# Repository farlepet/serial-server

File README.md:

Network-Connected Serial Server
===============================
This project intends to develop a simple and (relatively) low-cost Linux-based
network-connected (Ethernet or WiFi) serial (RS-232) device, that can act as
either a console server, or emulate a serial device such as a modem.

Intended hardware features
* Multiple power sources
  * PoE
  * USB (also doubles as serial debug port)
  * External power
* WiFi connection
  * Planning on ESP32-C3 via SPI (and maybe UART as fallback)
  * Use [esp-hosted](https://github.com/espressif/esp-hosted) to interface with Linux
  * Likely won't need any external flash, may design in the option just in case
* Ethernet connection
  * At least 10/100, undecided on specifics, SG2002 should already have a PHY,
    so should just need the port and magnetics (if not integrated, needs to
    support PoE).
* Linux-capable CPU
  * Planning on using SG2002 RISC-V SOC
  * Running Linux off of micro-SD card
    * Possible option for SPI flash?
* RS-232 via DE-9
  * Port pinout is as a DCE, as this is the most likely scenario in which the
    ring indicator would be useful. NULL-modem cable/adapter can be used to switch
    to DTE pinout.
  * Using MAX3237 transceiver to allow full functionality while in DCE mode
  * Headers availble to allow for custom daughter boards for different protocols
* Status LEDs
  * Separate serlal RX and TX LEDs
  * Possible ring-indicator LED
  * Possible "remote access active" LED
* Possibly integrating a security chip like the ATECC
* Possibly hardware watchdog

Use of third-party symbols/footprints
-------------------------------------

The following footprints were obtained from Digi-Key:
 * Amphenol 10067099-400LF: https://www.digikey.com/en/models/4238740

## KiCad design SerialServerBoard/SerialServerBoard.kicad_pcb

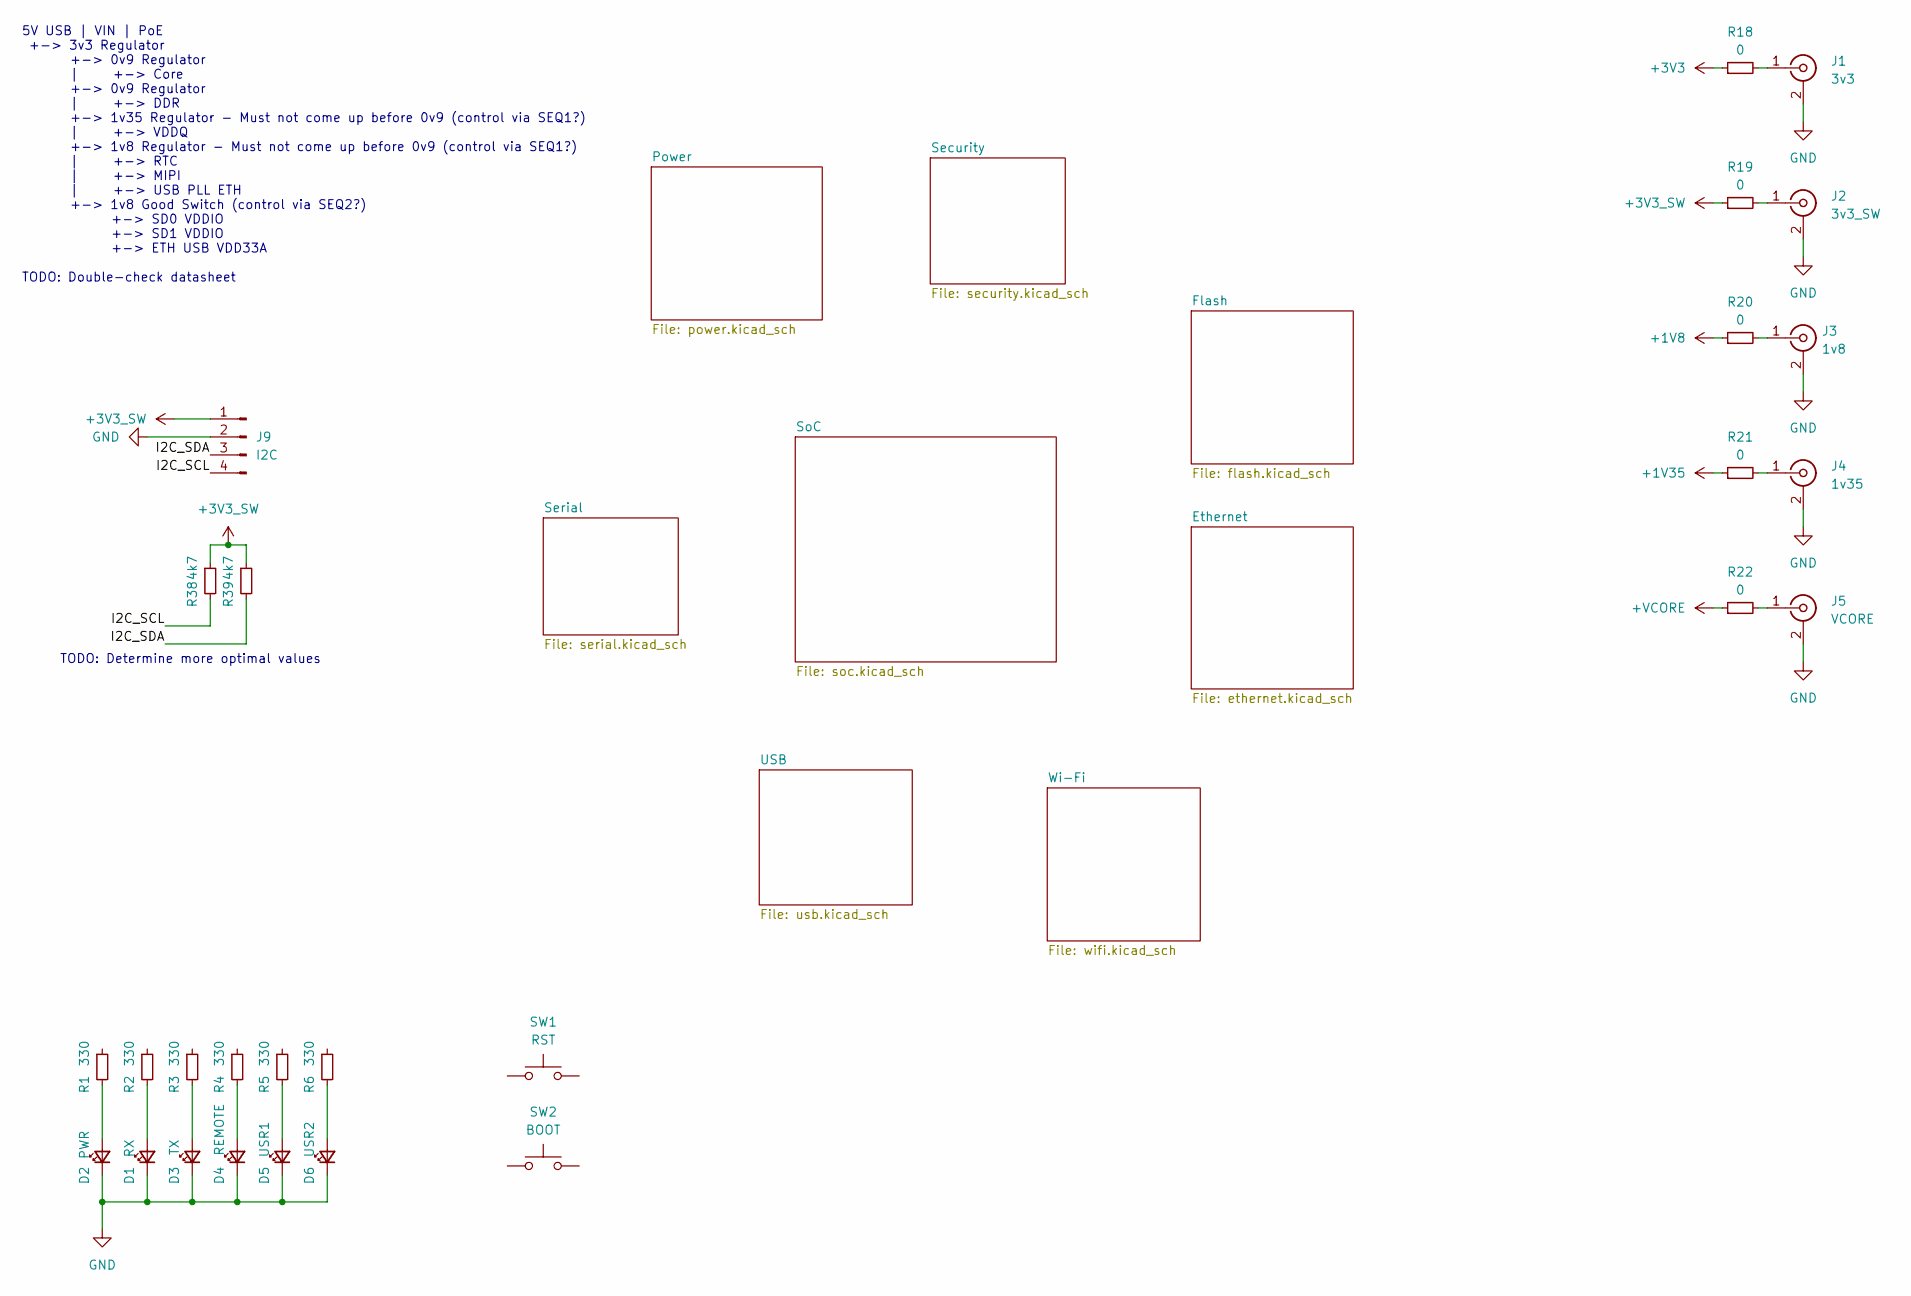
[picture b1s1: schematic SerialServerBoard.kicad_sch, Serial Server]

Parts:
D1: RX; LED_0603_1608Metric
D2: PWR; LED_0603_1608Metric
D3: TX; LED_0603_1608Metric
D4: REMOTE; LED_0603_1608Metric
D5: USR1; LED_0603_1608Metric
D6: USR2; LED_0603_1608Metric
J1: 3v3; TE_CONN_2337019-1
J2: 3v3_SW; TE_CONN_2337019-1
J3: 1v8; TE_CONN_2337019-1
J4: 1v35; TE_CONN_2337019-1
J5: VCORE; TE_CONN_2337019-1
J9: I2C; PinHeader_1x04_P1.27mm_Vertical
R1, R2, R3, R4, R5, R6: 330; R_0603_1608Metric
R18, R19, R20, R21, R22: 0; R_0402_1005Metric
R38, R39: 4k7; R_0603_1608Metric
SW1: RST
SW2: BOOT

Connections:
+1V8: R20.1; also elsewhere on the board
+1V35: R21.1; also elsewhere on the board
+3V3: R18.1
+3V3_SW: J9.1, R19.1, R38.1, R39.1; also elsewhere on the board
+VCORE: R22.1; also elsewhere on the board
/I2C_SCL: J9.4, R38.2
/I2C_SDA: J9.3, R39.2
GND: D1.1 (K), D2.1 (K), D3.1 (K), D4.1 (K), D5.1 (K), D6.1 (K), J1.2 (Ext), J2.2 (Ext), J3.2 (Ext), J4.2 (Ext), J5.2 (Ext), J9.2; also elsewhere on the board
unnamed: D1.2 (A), R2.2
unnamed: D2.2 (A), R1.2
unnamed: D3.2 (A), R3.2
unnamed: D4.2 (A), R4.2
unnamed: D5.2 (A), R5.2
unnamed: D6.2 (A), R6.2
unnamed: J1.1 (In), R18.2
unnamed: J2.1 (In), R19.2
unnamed: J3.1 (In), R20.2
unnamed: J4.1 (In), R21.2
unnamed: J5.1 (In), R22.2

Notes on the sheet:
TODO: Determine more optimal values
5V USB | VIN | PoE +-> 3v3 Regulator +-> 0v9 Regulator | +-> Core +-> 0v9 Regulator | +-> DDR +-> 1v35 Regulator - Must not come up before 0v9 (control via SEQ1?) | +-> VDDQ +-> 1v8 Regulator - Must not come up before 0v9 (control via SEQ1?) | +-> RTC | +-> MIPI | +-> USB PLL ETH +-> 1v8 Good Switc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

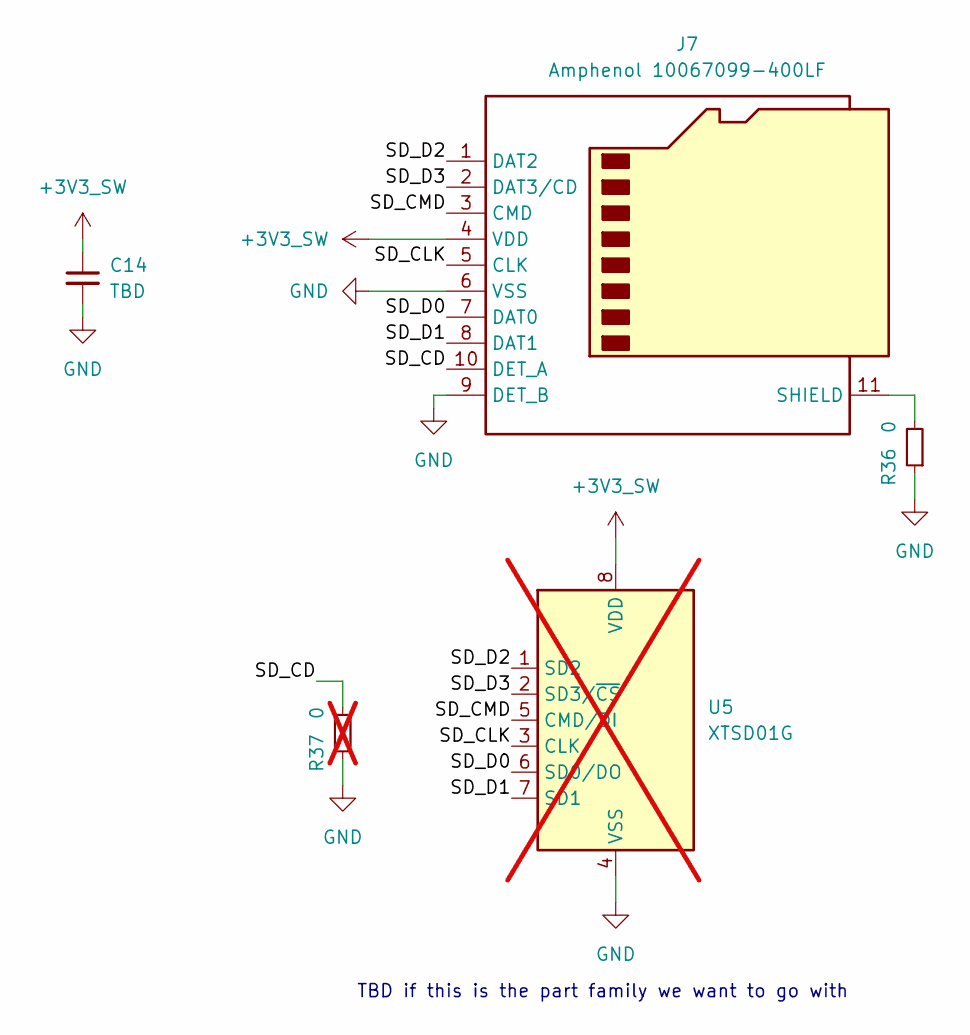
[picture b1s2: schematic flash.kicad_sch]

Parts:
C14: TBD; C_0603_1608Metric
J7: Amphenol 10067099-400LF; CONN8_10067099-400LF_FCI
R36: 0; R_0402_1005Metric
R37: 0; R_0402_1005Metric; not fitted
U5: XTSD01G; LGA-8_8x6mm_P1.27mm; not fitted

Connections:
+3V3_SW: C14.1, J7.4 (VDD), U5.8 (VDD); also elsewhere on the board
/Flash/SD_CD: J7.10 (DET_A), R37.2
/Flash/SD_CLK: J7.5 (CLK), U5.3 (CLK)
/Flash/SD_CMD: J7.3 (CMD), U5.5 (CMD/DI)
/Flash/SD_D0: J7.7 (DAT0), U5.6 (SD0/DO)
/Flash/SD_D1: J7.8 (DAT1), U5.7 (SD1)
/Flash/SD_D2: J7.1 (DAT2), U5.1 (SD2)
/Flash/SD_D3: J7.2 (DAT3/CD), U5.2 (SD3/~CS)
GND: C14.2, J7.6 (VSS), J7.9 (DET_B), R36.1, R37.1, U5.4 (VSS); also elsewhere on the board
unnamed: J7.11 (SHIELD), R36.2

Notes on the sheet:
TBD if this is the part family we want to go with

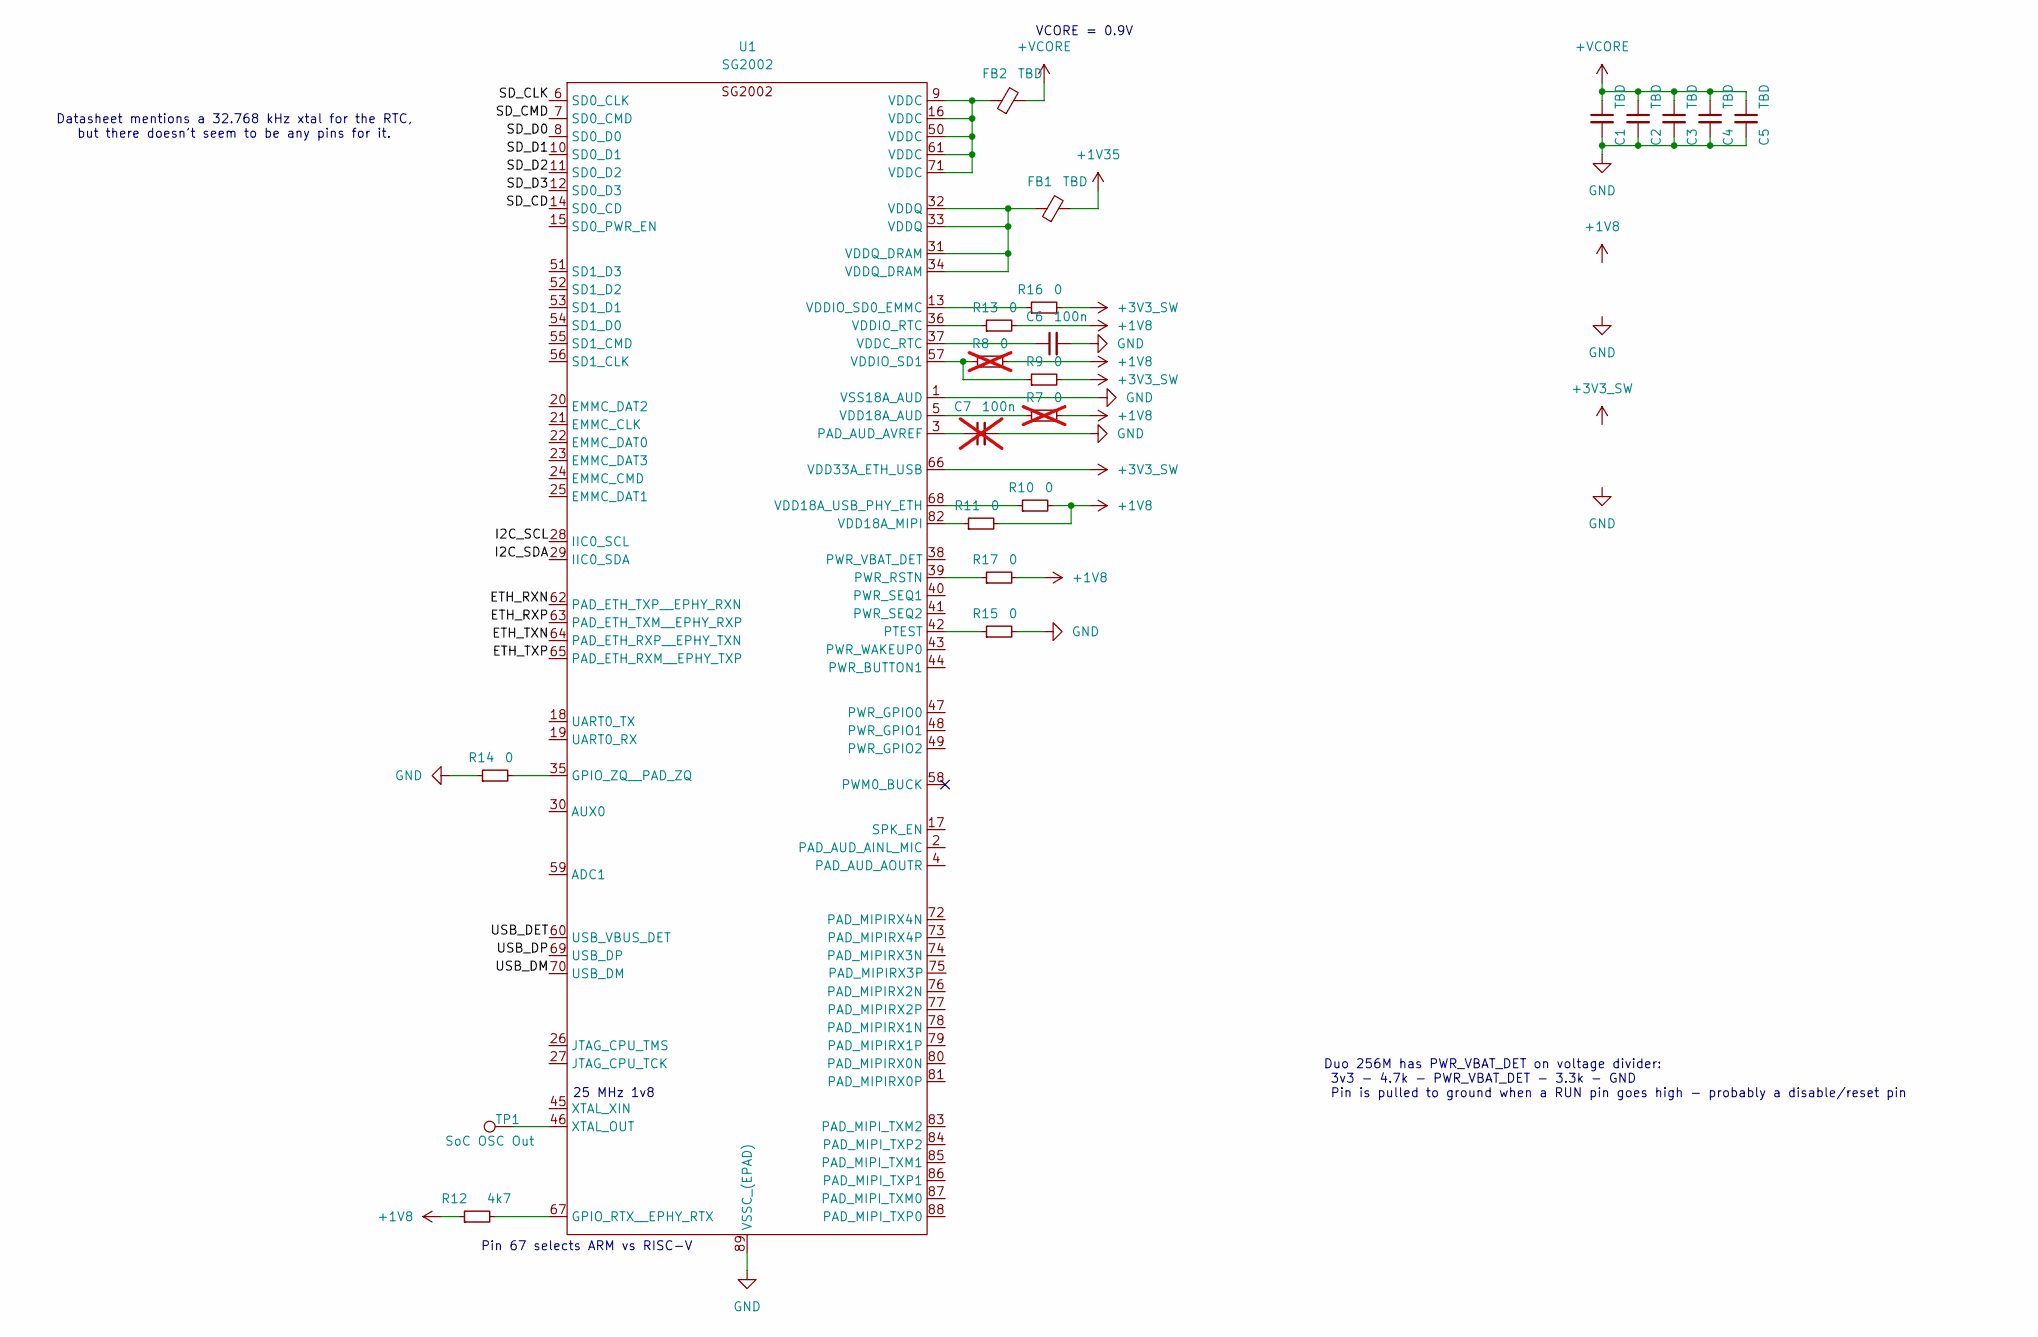
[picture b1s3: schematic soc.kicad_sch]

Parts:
C1, C2, C3, C4, C5: TBD; C_0603_1608Metric
C6: 100n
C7: 100n; not fitted
FB1, FB2: TBD; L_0603_1608Metric
R7, R8: 0; R_0402_1005Metric; not fitted
R9, R10, R11, R13, R14, R15, R16, R17: 0; R_0402_1005Metric
R12: 4k7; R_0603_1608Metric
TP1: SoC OSC Out
U1: SG2002; SG2002_QFN-88

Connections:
+1V8: R7.2, R8.2, R10.2, R11.2, R12.1, R13.2, R17.2; also elsewhere on the board
+1V35: FB1.2; also elsewhere on the board
+3V3_SW: R9.2, R16.2, U1.66 (VDD33A_ETH_USB); also elsewhere on the board
+VCORE: C1.1, C2.1, C3.1, C4.1, C5.1, FB2.2; also elsewhere on the board
/SoC/ETH_RXN: U1.62 (PAD_ETH_TXP__EPHY_RXN)
/SoC/ETH_RXP: U1.63 (PAD_ETH_TXM__EPHY_RXP)
/SoC/ETH_TXN: U1.64 (PAD_ETH_RXP__EPHY_TXN)
/SoC/ETH_TXP: U1.65 (PAD_ETH_RXM__EPHY_TXP)
/SoC/I2C_SCL: U1.28 (IIC0_SCL)
/SoC/I2C_SDA: U1.29 (IIC0_SDA)
/SoC/SD_CD: U1.14 (SD0_CD)
/SoC/SD_CLK: U1.6 (SD0_CLK)
/SoC/SD_CMD: U1.7 (SD0_CMD)
/SoC/SD_D0: U1.8 (SD0_D0)
/SoC/SD_D1: U1.10 (SD0_D1)
/SoC/SD_D2: U1.11 (SD0_D2)
/SoC/SD_D3: U1.12 (SD0_D3)
/SoC/USB_DET: U1.60 (USB_VBUS_DET)
/SoC/USB_DM: U1.70 (USB_DM)
/SoC/USB_DP: U1.69 (USB_DP)
GND: C1.2, C2.2, C3.2, C4.2, C5.2, C6.2, C7.2, R14.1, R15.2, U1.1 (VSS18A_AUD), U1.89 (VSSC_(EPAD)); also elsewhere on the board
unnamed: FB1.1, U1.31 (VDDQ_DRAM), U1.32 (VDDQ), U1.33 (VDDQ), U1.34 (VDDQ_DRAM)
unnamed: FB2.1, U1.9 (VDDC), U1.16 (VDDC), U1.50 (VDDC), U1.61 (VDDC), U1.71 (VDDC)
unnamed: R12.2, U1.67 (GPIO_RTX__EPHY_RTX)
unnamed: R14.2, U1.35 (GPIO_ZQ__PAD_ZQ)
unnamed: C7.1, U1.3 (PAD_AUD_AVREF)
unnamed: R15.1, U1.42 (PTEST)
unnamed: R17.1, U1.39 (PWR_RSTN)
unnamed: R7.1, U1.5 (VDD18A_AUD)
unnamed: R11.1, U1.82 (VDD18A_MIPI)
unnamed: R10.1, U1.68 (VDD18A_USB_PHY_ETH)
unnamed: C6.1, U1.37 (VDDC_RTC)
unnamed: R13.1, U1.36 (VDDIO_RTC)
unnamed: R16.1, U1.13 (VDDIO_SD0_EMMC)
unnamed: R8.1, R9.1, U1.57 (VDDIO_SD1)
unnamed: TP1.1, U1.46 (XTAL_OUT)

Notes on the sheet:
Pin 67 selects ARM vs RISC-V
Datasheet mentions a 32.768 kHz xtal for the RTC, but there doesn't seem to be any pins for it.
Duo 256M has PWR_VBAT_DET on voltage divider: 3v3 - 4.7k - PWR_VBAT_DET - 3.3k - GND Pin is pulled to ground when a RUN pin goes high - probably a disable/reset pin
25 MHz 1v8
VCORE = 0.9V

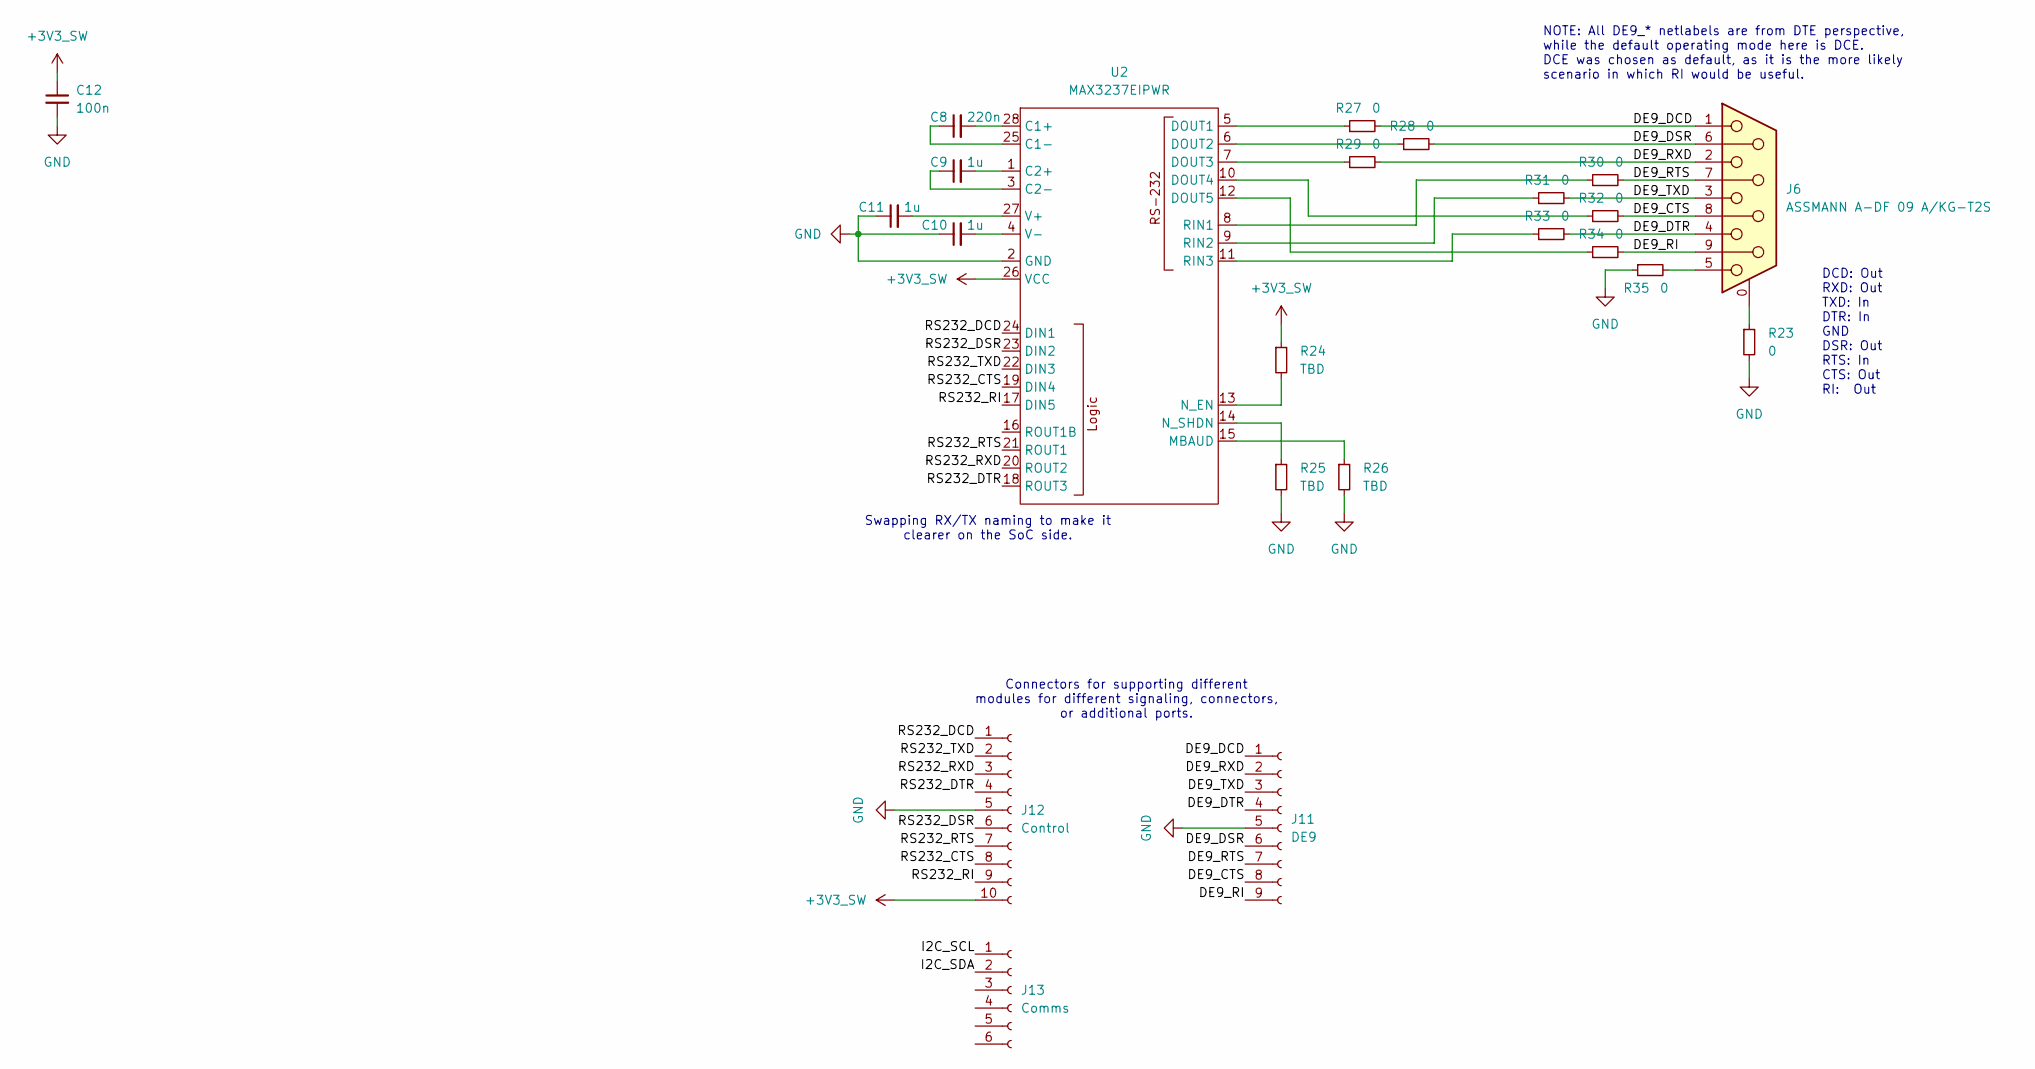
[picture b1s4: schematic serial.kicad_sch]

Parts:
C8: 220n; C_0603_1608Metric
C9, C10, C11: 1u; C_0603_1608Metric
C12: 100n; C_0603_1608Metric
J6: ASSMANN A-DF 09 A/KG-T2S; ASSMANN_A-DF_09_A_KG-T2S
J11: DE9; PinHeader_1x09_P1.27mm_Vertical
J12: Control; PinHeader_1x10_P1.27mm_Vertical
J13: Comms; PinHeader_1x06_P1.27mm_Vertical
R23, R27, R28, R29, R30, R31, R32, R33, R34, R35: 0; R_0402_1005Metric
R24, R25, R26: TBD; R_0402_1005Metric
U2: MAX3237EIPWR; TSSOP-28_4.4x9.7mm_P0.65mm

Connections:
+3V3_SW: C12.1, J12.10, R24.1, U2.26 (VCC); also elsewhere on the board
/Serial/DE9_CTS: J6.8, J11.8, R32.2
/Serial/DE9_DCD: J6.1, J11.1, R27.2
/Serial/DE9_DSR: J6.6, J11.6, R28.2
/Serial/DE9_DTR: J6.4, J11.4, R33.2
/Serial/DE9_RI: J6.9, J11.9, R34.2
/Serial/DE9_RTS: J6.7, J11.7, R30.2
/Serial/DE9_RXD: J6.2, J11.2, R29.2
/Serial/DE9_TXD: J6.3, J11.3, R31.2
/Serial/I2C_SCL: J13.1
/Serial/I2C_SDA: J13.2
/Serial/RS232_CTS: J12.8, U2.19 (DIN4)
/Serial/RS232_DCD: J12.1, U2.24 (DIN1)
/Serial/RS232_DSR: J12.6, U2.23 (DIN2)
/Serial/RS232_DTR: J12.4, U2.18 (ROUT3)
/Serial/RS232_RI: J12.9, U2.17 (DIN5)
/Serial/RS232_RTS: J12.7, U2.21 (ROUT1)
/Serial/RS232_RXD: J12.3, U2.20 (ROUT2)
/Serial/RS232_TXD: J12.2, U2.22 (DIN3)
GND: C10.1, C11.1, C12.2, J11.5, J12.5, R23.2, R25.2, R26.2, R35.1, U2.2 (GND); also elsewhere on the board
unnamed: J6.0 (PAD), R23.1
unnamed: J6.5, R35.2
unnamed: C8.2, U2.28 (C1+)
unnamed: C8.1, U2.25 (C1-)
unnamed: C9.2, U2.1 (C2+)
unnamed: C9.1, U2.3 (C2-)
unnamed: R27.1, U2.5 (DOUT1)
unnamed: R28.1, U2.6 (DOUT2)
unnamed: R29.1, U2.7 (DOUT3)
unnamed: R32.1, U2.10 (DOUT4)
unnamed: R34.1, U2.12 (DOUT5)
unnamed: R26.1, U2.15 (MBAUD)
unnamed: R24.2, U2.13 (N_EN)
unnamed: R25.1, U2.14 (N_SHDN)
unnamed: R30.1, U2.8 (RIN1)
unnamed: R31.1, U2.9 (RIN2)
unnamed: R33.1, U2.11 (RIN3)
unnamed: C11.2, U2.27 (V+)
unnamed: C10.2, U2.4 (V-)

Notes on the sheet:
Connectors for supporting different modules for different signaling, connectors, or additional ports.
DCD: Out RXD: Out TXD: In DTR: In GND DSR: Out RTS: In CTS: Out RI: Out
Swapping RX/TX naming to make it clearer on the SoC side.
NOTE: All DE9_* netlabels are from DTE perspective, while the default operating mode here is DCE. DCE was chosen as default, as it is the more likely scenario in which RI would be useful.

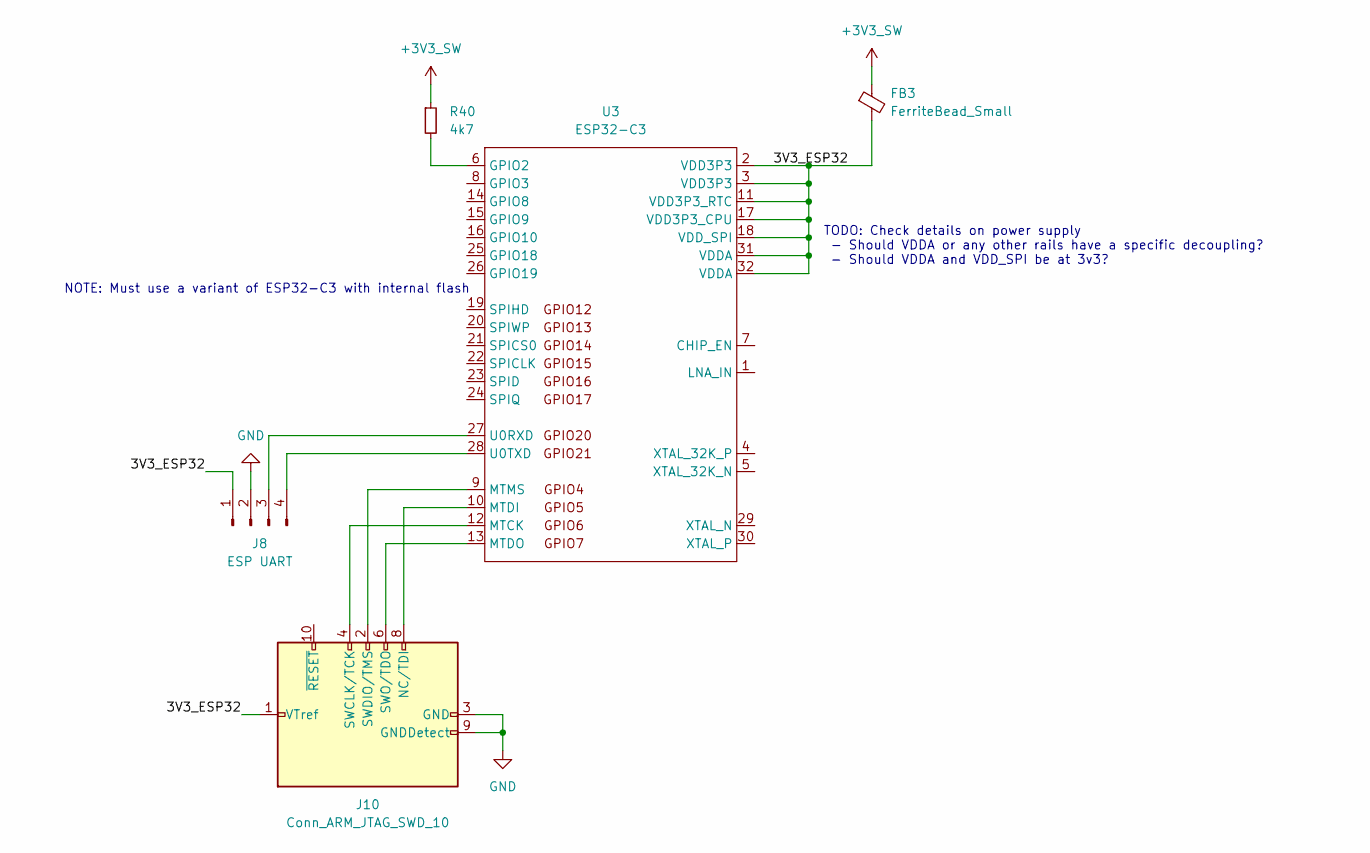
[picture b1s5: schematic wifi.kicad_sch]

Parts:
FB3: FerriteBead_Small; L_0603_1608Metric
J8: ESP UART; PinSocket_1x04_P1.27mm_Vertical
J10: Conn_ARM_JTAG_SWD_10; PinSocket_2x05_P1.27mm_Vertical
R40: 4k7; R_0402_1005Metric
U3: ESP32-C3

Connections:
+3V3_SW: FB3.1, R40.1; also elsewhere on the board
/Wi-Fi/3V3_ESP32: FB3.2, J8.1, J10.1 (VTref), U3.2 (VDD3P3), U3.3 (VDD3P3), U3.11 (VDD3P3_RTC), U3.17 (VDD3P3_CPU), U3.18 (VDD_SPI), U3.31 (VDDA), U3.32 (VDDA)
GND: J8.2, J10.3 (GND), J10.5 (GND), J10.9 (GNDDetect); also elsewhere on the board
unnamed: J8.3, U3.27 (U0RXD)
unnamed: J8.4, U3.28 (U0TXD)
unnamed: J10.8 (NC/TDI), U3.10 (MTDI)
unnamed: J10.4 (SWCLK/TCK), U3.12 (MTCK)
unnamed: J10.2 (SWDIO/TMS), U3.9 (MTMS)
unnamed: J10.6 (SWO/TDO), U3.13 (MTDO)
unnamed: R40.2, U3.6 (GPIO2)

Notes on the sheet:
NOTE: Must use a variant of ESP32-C3 with internal flash
TODO: Check details on power supply - Should VDDA or any other rails have a specific decoupling? - Should VDDA and VDD_SPI be at 3v3?

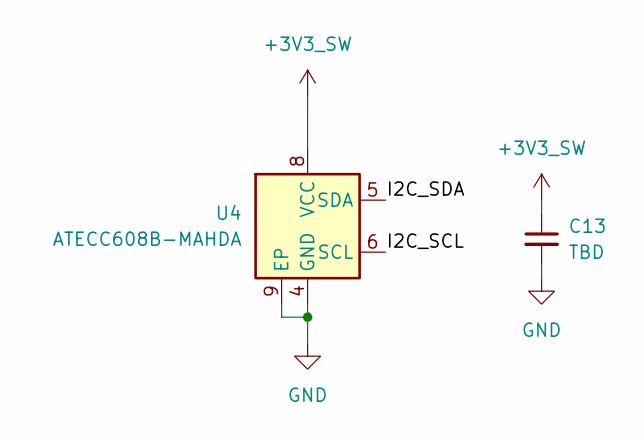
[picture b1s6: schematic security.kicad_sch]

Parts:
C13: TBD; C_0603_1608Metric
U4: ATECC608B-MAHDA; DFN-8-1EP_3x2mm_P0.5mm_EP1.3x1.5mm

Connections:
+3V3_SW: C13.1, U4.8 (VCC); also elsewhere on the board
/Security/I2C_SCL: U4.6 (SCL)
/Security/I2C_SDA: U4.5 (SDA)
GND: C13.2, U4.4 (GND), U4.9 (EP); also elsewhere on the board

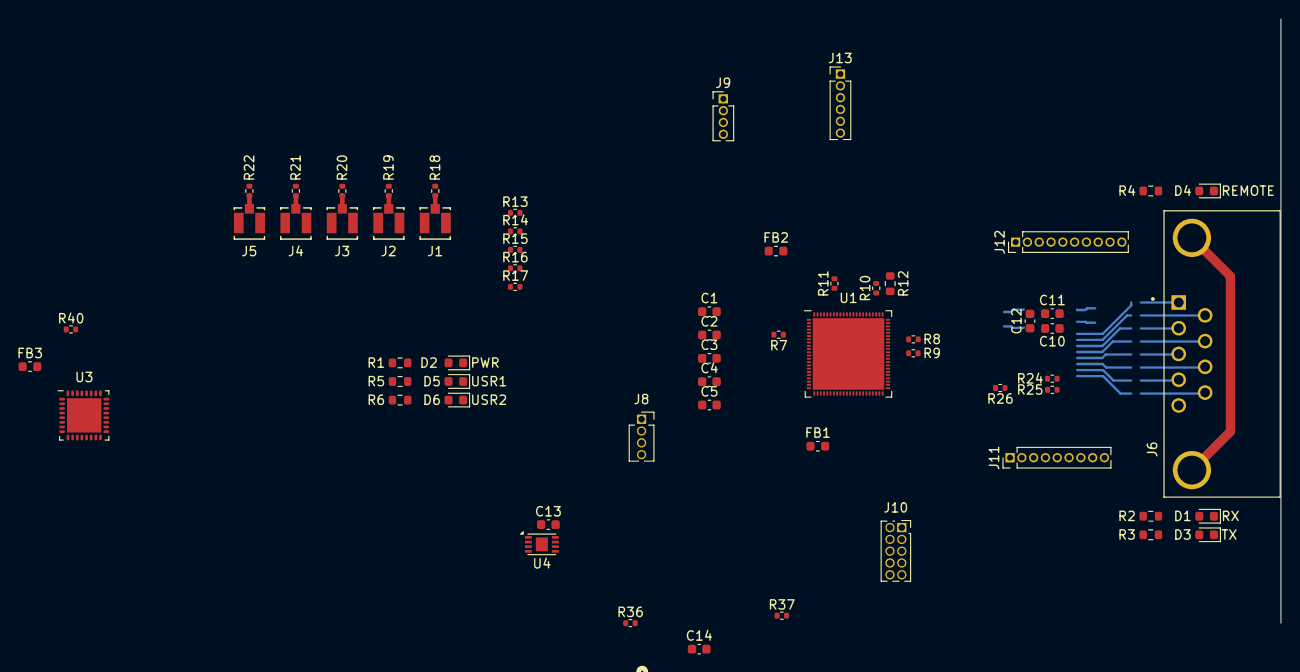
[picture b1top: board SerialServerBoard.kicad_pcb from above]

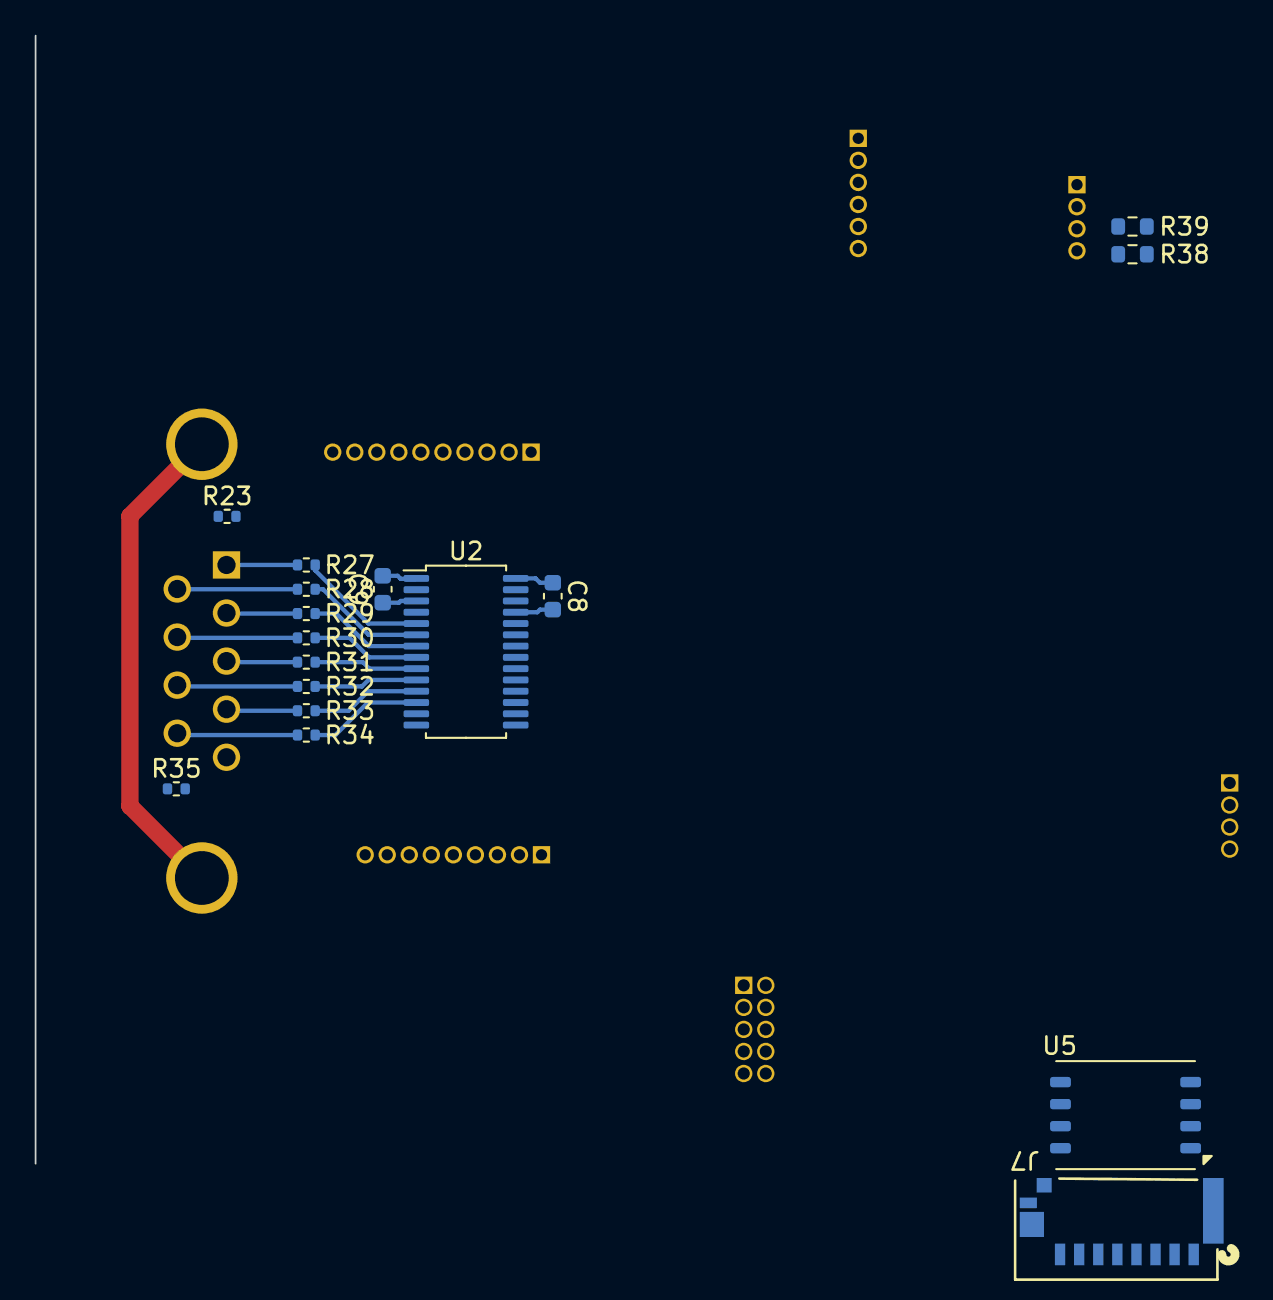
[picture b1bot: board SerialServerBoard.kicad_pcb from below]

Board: 2 copper layers, 79 parts (17 on the bottom side), 81 nets.

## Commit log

2024-04-14 Add ESP32-C3 footprint
2024-05-09 Add ATECC
2024-07-05 Add micro-SD card slot
